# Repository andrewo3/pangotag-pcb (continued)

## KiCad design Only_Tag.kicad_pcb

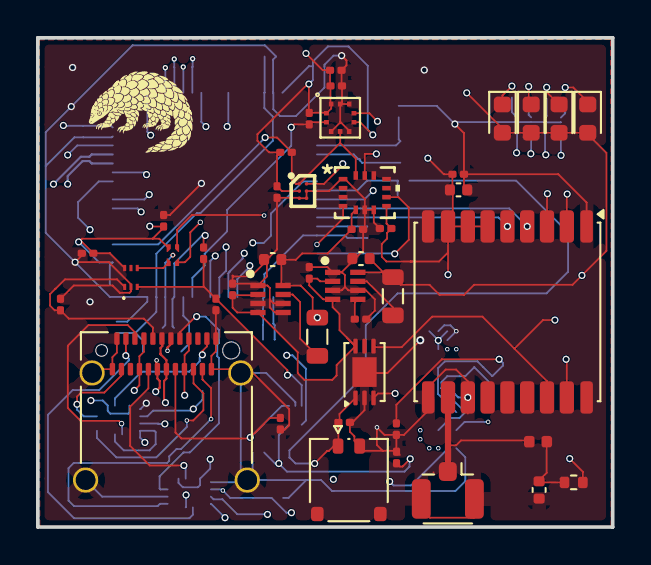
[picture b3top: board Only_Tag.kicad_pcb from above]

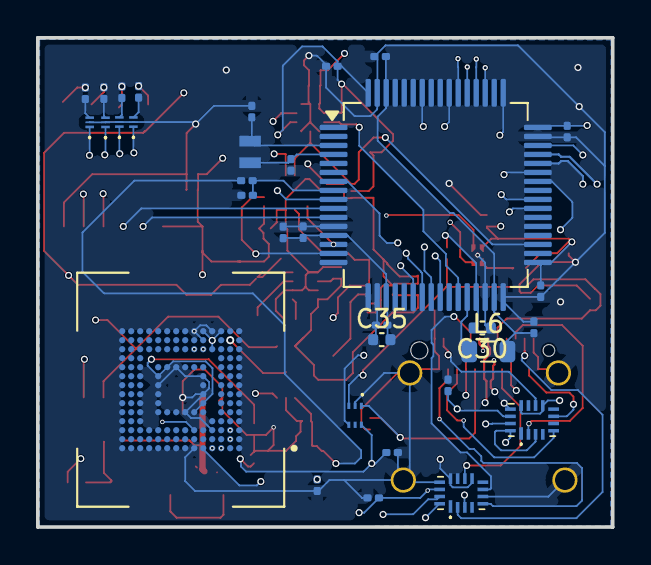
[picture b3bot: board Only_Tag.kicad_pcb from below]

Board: 6 copper layers, 31.9 x 27.2 mm, 77 parts (33 on the bottom side), 64 nets.

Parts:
C1, C2, C3, C10, C15, C18, C20, C21, C23, C26, C27, C28, C29, C31, C32, C36, C37, C39, C40: 100n; C_0201_0603Metric
C4: 10n; C_0402_1005Metric
C7, C8: 4.7u; C_0201_0603Metric
C13: 0.1u; C_0201_0603Metric
C16, C17: 8p; C_0201_0603Metric
C22, C24, C25, C30, C35: 10u; C_0402_1005Metric
C38: 1u; C_0201_0603Metric
C41, C42: 2.2u; C_0201_0603Metric
D1: XZCM2CRK53WA-1VF; LED_0603_1608Metric
D2: XZCM2CYK53WA-1VF; LED_0603_1608Metric
D3: XZCDGK53W-1VF; LED_0603_1608Metric
D4: XZCFBB53W-1VF; LED_0603_1608Metric
IC1, IC2: TLV3691IDPFR
IC3, IC4: TPS62840DLCR; SON50P150X200X100-8N-D
IC5, IC6: TS3A5018RSVR
J1: USB_C_Receptacle; USB_C_Receptacle_Amphenol_12401610E4-2A_CircularHoles
J2: Conn_Coaxial; U.FL_Hirose_U.FL-R-SMT-1_Vertical
J5: Conn_01x02; Hirose_DF57H-2P-1.2V_1x02_P1.2mm_Socket
L1: 27n; L_0402_1005Metric
L5, L6, L7: 2.2u; L_0805_2012Metric
Q1, Q2, Q3, Q4: PMX100UNZ
R1, R2: 10k; R_0201_0603Metric
R3, R4: 5.1k; R_0201_0603Metric
R5: 10; R_0402_1005Metric
R6: 900; R_0201_0603Metric
R7: 725; R_0201_0603Metric
R8, R9: 325; R_0201_0603Metric
R13: 267k; R_0201_0603Metric
R15: 1M; R_0201_0603Metric
R16: 500k; R_0201_0603Metric
R21: 80M; R_0201_0603Metric
R22: 10M; R_0201_0603Metric
U2: NSEC3T016-IT; BGA153N50P14X14_1150X1300X80
U3: SN74AUP1G08DPWR; DPW0005A_TEX
U4: MAX-M10S; ublox_MAX
U7: LTC2941IDCB-1#TRMPBF; DFN-6-1EP_3x2mm_P0.5mm_EP1.65x1.35mm
U8: STM32U585RITxQ; LQFP-64_10x10mm_P0.5mm
U11: AS6221T-AWLT; BGA6C40P2X3_102X150X52
U14: BMP581
U16: BMI270; BMI270_BOS
Y1: CM9V-T1A-32.768KHZ-7PF-20PPM-TA-QC; XTAL_CM9V-T1A-32.768KHZ-7PF-20PPM-TA-QC

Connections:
+3V3: C2.2, C24.1, C29.2, D1.2 (A), D2.2 (A), D3.2 (A), D4.2 (A), IC3.8 (VOS), L5.1, R5.1, U2.E6 (VCC), U2.F5 (VCC), U2.J10 (VCC), U2.K9 (VCC), U8.48 (VDDUSB)
ACC_INT1: U8.14 (PA0), U16.4 (INT1)
ACC_INT2: U8.15 (PA1), U16.9 (INT2)
CC1: IC1.1 (IN+), J1.A5 (CC1), R3.1
CC2: IC2.1 (IN+), J1.B5 (CC2), R4.1
GND: C1.2, C2.1, C3.2, C4.2, C7.2, C8.2, C10.2, C13.2, C15.2, C16.1, C17.1, C18.2, C20.1, C21.2, C22.2, C23.2, C24.2, C25.2, C26.2, C27.2, C28.2, C29.1, C30.1, C31.2, C32.2, C35.1, C36.1, C37.1, C38.1, C39.1, C40.1, C41.2, C42.2, IC1.2 (GND), IC2.2 (GND), IC3.1 (GND), IC3.3 (MODE), IC3.6 (STOP), IC4.1 (GND), IC4.3 (MODE), IC4.5 (VSET), IC4.6 (STOP), IC5.6 (GND), IC5.13 (~EN), IC6.13 (~EN), J1.A1 (GND), J1.A12 (GND), J1.B1 (GND), J1.B12 (GND), J1.SH (SHIELD), J2.2 (Ext), J5.2, Q1.2 (S), Q2.2 (S), Q3.2 (S), Q4.2 (S), R3.2, R4.2, R13.2, R16.2, R22.2, U2.A6 (VSS), U2.C4 (VSSQ), U2.E7 (VSS), U2.G5 (VSS), U2.H10 (VSS), U2.J5 (VSS), U2.K8 (VSS), U2.N2 (VSSQ), U2.N5 (VSSQ), U2.P4 (VSSQ), U2.P6 (VSSQ), U3.3 (GND), U4.1 (GND), U4.10 (GND), U4.12 (GND), U7.2 (GND), U7.7 (EP), U8.12 (VSSA), U8.18 (VSS), U8.30 (VSSSMPS), U8.32 (VSS), U8.47 (VSS), U8.63 (VSS), U11.B2 (VSS), U11.C1 (ADD0), U11.C2 (ALERT), U14.3 (GND), U14.5 (SDO/ADR), U14.8 (GND), U14.9 (GND), U16.1 (SDO), U16.6 (GNDIO), U16.7 (GND)
GPS_EXTINT: U4.5 (EXTINT), U8.11 (PC3)
I2C1_SCL: R1.1, U4.17 (SCL), U7.3 (SCL), U8.27 (PB10), U11.A2 (SCL), U14.2 (SCK/SCL), U16.13 (SCX)
I2C1_SDA: R2.1, U4.16 (SDA), U7.4 (SDA), U8.35 (PB14), U11.A1 (SDA), U14.4 (SDI/SDA), U16.14 (SDX)
LED1: Q1.1 (G), U8.25 (PB1)
LED2: Q2.1 (G), U8.24 (PB0)
LED3: Q3.1 (G), U8.23 (PA7)
LED4: Q4.1 (G), U8.22 (PA6)
NRST: IC5.9 (NC3), IC5.12 (NC4), U8.7 (NRST)
unnamed: C4.1, L1.1, R5.2
unnamed: C41.1, C42.1, L6.2, U8.31 (VDD11), U8.62 (VDD11)
unnamed: D1.1 (K), R6.2
unnamed: D2.1 (K), R7.2
unnamed: D3.1 (K), R8.2
unnamed: D4.1 (K), R9.2
unnamed: IC1.3 (IN-), IC2.3 (IN-), R21.2, R22.1
unnamed: IC1.4 (OUT), U3.1 (A)
unnamed: IC2.4 (OUT), U3.2 (B)
unnamed: IC3.7 (SW), L5.2
unnamed: IC3.5 (VSET), R13.1
unnamed: IC4.7 (SW), L7.2
unnamed: IC5.2 (COM1), J1.A2 (TX1+)
unnamed: IC5.5 (COM2), J1.B2 (TX2+)
unnamed: IC5.7 (COM3), J1.A8 (SBU1)
unnamed: IC5.10 (COM4), J1.B8 (SBU2)
unnamed: IC6.2 (COM1), J1.A3 (TX1-)
unnamed: IC6.5 (COM2), J1.B3 (TX2-)
unnamed: IC6.7 (COM3), J1.B11 (RX1+)
unnamed: IC6.10 (COM4), J1.A11 (RX2+)
unnamed: Q1.3 (D), R6.1
unnamed: Q2.3 (D), R7.1
unnamed: Q3.3 (D), R8.1
unnamed: Q4.3 (D), R9.1
unnamed: C3.1, U2.C2 (VDDi)
OSC32_IN: C17.2, U8.3 (PC14), Y1.2
OSC32_OUT: C16.2, U8.4 (PC15), Y1.1
PRS_INT: U8.9 (PC1), U14.7 (INT)
RF_IN: J2.1 (In), L1.2, U4.11 (RF_IN)
SDMMC1_CK: U2.M6 (CLK), U8.53 (PC12)
SDMMC1_CMD: U2.M5 (CMD), U8.54 (PD2)
SDMMC1_D0: U2.A3 (DAT0), U8.39 (PC8)
SDMMC1_D1: U2.A4 (DAT1), U8.40 (PC9)
SDMMC1_D2: U2.A5 (DAT2), U8.51 (PC10)
SDMMC1_D3: U2.B2 (DAT3), U8.52 (PC11)
SWCLK: IC5.3 (NC2), IC5.16 (NC1), U8.49 (PA14)
SWDIO: IC6.3 (NC2), IC6.16 (NC1), U8.46 (PA13)
SWO: IC6.9 (NC3), IC6.12 (NC4), U8.55 (PB3)
Timepulse: U4.4 (TIMEPULSE), U8.10 (PC2)
USART1_RX: U4.2 (TXD), U8.43 (PA10)
USART1_TX: U4.3 (RXD), U8.58 (PB6)
USBC_FUNCTION: IC5.15 (IN), IC6.15 (IN), U3.4 (Y)
USB_OTG_FS_D+: J1.A6 (D+), J1.B6 (D+), U8.45 (PA12)
USB_OTG_FS_D-: J1.A7 (D-), J1.B7 (D-), U8.44 (PA11)
USB_OTG_VBUS: J1.A4 (VBUS), J1.A9 (VBUS), J1.B4 (VBUS), J1.B9 (VBUS), U8.42 (PA9)
VBAT/3: R15.2, R16.1, U8.8 (PC0)
VDD: C13.1, J5.1, R15.1, U7.1 (SENSE+)
VDD2: C7.1, C8.1, IC3.2 (VIN), IC3.4 (EN), IC4.2 (VIN), IC4.4 (EN), U7.6 (SENSE–)
VDDA: C1.1, C10.1, C15.1, C18.1, C20.2, C21.1, C22.1, C23.1, C25.1, C26.1, C27.1, C28.1, C30.2, C31.1, C32.1, C35.2, C36.2, C37.2, C38.2, C39.2, C40.2, IC1.6 (VCC), IC2.6 (VCC), IC4.8 (VOS), IC5.14 (V+), IC6.14 (V+), L7.1, R1.2, R2.2, R21.1, U2.C6 (VCCQ), U2.M4 (VCCQ), U2.N4 (VCCQ), U2.P3 (VCCQ), U2.P5 (VCCQ), U3.5 (VCC), U4.6 (V_BCKP), U4.7 (VCC_IO), U4.8 (VCC), U8.13 (VDDA), U8.19 (VDD), U8.29 (VDDSMPS), U8.33 (VDD), U8.64 (VDD), U11.B1 (VDD), U14.1 (VDDIO), U14.6 (CSB), U14.10 (VDD), U16.5 (VDDIO), U16.8 (VDD)
VLXSMPS: L6.1, U8.28 (VLXSMPS)

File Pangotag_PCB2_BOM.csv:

"Id";"Designator";"Footprint";"Quantity";"Designation";"Supplier and ref";
1;"BT1, BT2, BT3";"BAT_2996";3;"2996";;;
2;"C1, C2, C3, C10, C15, C18, C20, C21, C23, C26, C27, C28, C29, C31, C32, C36, C37, C39, C40";"C_0201_0603Metric";19;"100n";;;
3;"C7, C8, C11";"C_0201_0603Metric";3;"4.7u";;;
4;"C13";"C_0201_0603Metric";1;"0.1u";;;
5;"C16, C17";"C_0201_0603Metric";2;"8p";;;
6;"C19, C22, C24, C25, C30, C35";"C_0201_0603Metric";6;"10u";;;
7;"C38";"C_0201_0603Metric";1;"1u";;;
8;"C41, C42";"C_0201_0603Metric";2;"2.2u";;;
9;"CN2";"PinHeader_2x03_P2.54mm_Vertical";1;"POGOPIN_2X04_P2.54_M";;;
10;"D1";"LED_0201_0603Metric";1;"XZCM2CRK53WA-1VF";;;
11;"D2";"LED_0201_0603Metric";1;"XZCM2CYK53WA-1VF";;;
12;"D3";"LED_0201_0603Metric";1;"XZCDGK53W-1VF";;;
13;"D4";"LED_0201_0603Metric";1;"XZCFBB53W-1VF";;;
14;"IC1, IC2";"TLV3691IDPFR";2;"TLV3691IDPFR";;;
15;"IC3, IC4";"SON50P150X200X100-8N-D";2;"TPS62840DLCR";;;
16;"IC5, IC6";"TS3A5018RSVR";2;"TS3A5018RSVR";;;
17;"J1";"USB_C_Receptacle_Amphenol_12401610E4-2A_CircularHoles";1;"USB_C_Receptacle";;;
18;"J2";"U.FL_Hirose_U.FL-R-SMT-1_Vertical";1;"Conn_Coaxial";;;
19;"J3";"USB_Mini-B_Lumberg_2486_01_Horizontal";1;"USB_B_Mini";;;
20;"J4";"UP32CFGFL3P24TR";1;"UP32-C-F-G-FL-3-P24-TR";;;
21;"J5, J6, J7";"Hirose_DF57H-2P-1.2V_1x02_P1.2mm_Socket";3;"Conn_01x02";;;
22;"L1";"L_0201_0603Metric";1;"100n";;;
23;"L4, L5, L6, L7";"L_0201_0603Metric";4;"2.2u";;;
24;"Q1, Q2, Q3, Q4";"PMX100UNZ";4;"PMX100UNZ";;;
25;"R1, R2, R12";"R_0201_0603Metric";3;"10k";;;
26;"R3, R4";"R_0201_0603Metric";2;"5.1k";;;
27;"R6";"R_0201_0603Metric";1;"900";;;
28;"R7";"R_0201_0603Metric";1;"725";;;
29;"R8, R9";"R_0201_0603Metric";2;"325";;;
30;"R10, R17";"R_0201_0603Metric";2;"56k";;;
31;"R13";"R_0201_0603Metric";1;"267k";;;
32;"R15";"R_0201_0603Metric";1;"1M";;;
33;"R16";"R_0201_0603Metric";1;"500k";;;
34;"R21";"R_0201_0603Metric";1;"80M";;;
35;"R22";"R_0201_0603Metric";1;"10M";;;
36;"SW1";"SW_SPST_B3U-1000P";1;"SW_Push";;;
37;"U2";"BGA153N50P14X14_1150X1300X80";1;"~";;;
38;"U3";"DPW0005A_TEX";1;"SN74AUP1G08DPWR";;;
39;"U4";"ublox_MAX";1;"MAX-M10S";;;
40;"U7";"DFN-6-1EP_3x2mm_P0.5mm_EP1.65x1.35mm";1;"LTC2941IDCB-1#TRMPBF";;;
41;"U8";"LQFP-64_10x10mm_P0.5mm";1;"STM32U585RITxQ";;;
42;"U11";"BGA6C40P2X3_102X150X52";1;"AS6221T-AWLT";;;
43;"U14";"BMP581";1;"BMP581";;;
44;"U16";"BMI270_BOS";1;"BMI270";;;
45;"U18";"BGA6N40P3X2_146X96X50N";1;"TPS62840YBGR";;;
46;"Y1";"XTAL_CM9V-T1A-32.768KHZ-7PF-20PPM-TA-QC";1;"CM9V-T1A-32.768KHZ-7PF-20PPM-TA-QC";;;

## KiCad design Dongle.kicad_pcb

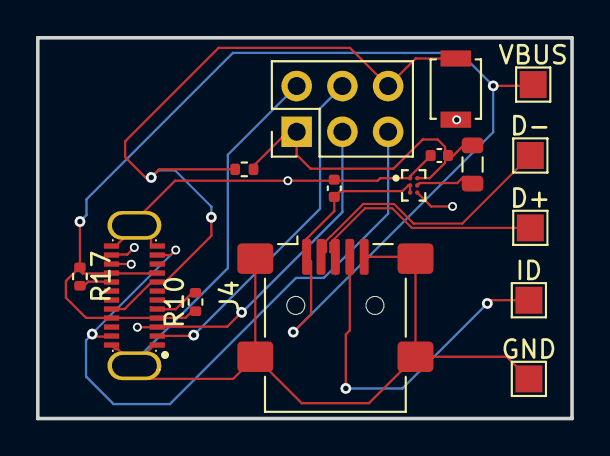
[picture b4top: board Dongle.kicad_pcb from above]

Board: 4 copper layers, 29.7 x 21.2 mm, 16 parts (0 on the bottom side), 13 nets.

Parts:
C11: 4.7u; C_0402_1005Metric
C19: 10u; C_0402_1005Metric
CN2: POGOPIN_2X04_P2.54_M; PinHeader_2x03_P2.54mm_Vertical
D+: MountingHole_Pad; TestPoint_Pad_1.5x1.5mm
D-: MountingHole_Pad; TestPoint_Pad_1.5x1.5mm
GND: MountingHole_Pad; TestPoint_Pad_1.5x1.5mm
ID: MountingHole_Pad; TestPoint_Pad_1.5x1.5mm
J3: USB_B_Mini; USB_Mini-B_Lumberg_2486_01_Horizontal
J4: UP32-C-F-G-FL-3-P24-TR; USB-TH-TYPE-C_00702-UCAM002-X
L4: 2.2u; L_0805_2012Metric
R10, R17: 56k; R_0402_1005Metric
R12: 10k; R_0402_1005Metric
SW1: SW_Push; SW_SPST_B3U-1000P
U18: TPS62840YBGR; BGA6N40P3X2_146X96X50N
VBUS: MountingHole_Pad; TestPoint_Pad_1.5x1.5mm

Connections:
+1V8_2: C19.1, CN2.1, L4.2, R12.1, U18.A2 (VOS)
GND2: C11.2, C19.2, CN2.2, GND.1 (1_1), J3.5 (GND), J3.SH (Shield), J4.14, J4.A1 (GND_1), J4.A12 (GND_2), J4.B1 (GND_3), J4.B12 (GND_4), SW1.2, U18.A1 (GND), U18.C2 (VSET)
NRST_OUT: CN2.6, J4.A8 (SBU1), J4.B8 (SBU2), R12.2, SW1.1
unnamed: ID.1 (1_1), J3.4 (ID)
unnamed: J4.A5 (CC1), R10.2
unnamed: J4.B5 (CC2), R17.2
unnamed: L4.1, U18.B2 (SW)
ST_D+: D+.1 (1_1), J3.3 (D+)
ST_D-: D-.1 (1_1), J3.2 (D-)
SWCLK_OUT: CN2.4, J4.A2 (SSTXP1), J4.B2 (SSTXP2)
SWDIO_OUT: CN2.3, J4.A3 (SSTXN1), J4.B3 (SSTXN2)
SWO_OUT: CN2.5, J4.A11 (SSRXP2), J4.B11 (SSRXP1)
VBUS_DONGLE: C11.1, J3.1 (VBUS), J4.A4 (VBUS_1), J4.A9 (VBUS_2), J4.B4 (VBUS_3), J4.B9 (VBUS_4), R10.1, R17.1, U18.B1 (VIN), U18.C1 (EN), VBUS.1 (1_1)

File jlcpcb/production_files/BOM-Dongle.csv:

Comment,Designator,Footprint,LCSC,Quantity
10k,R12,R_0402_1005Metric,C60489,1
10u,C19,C_0402_1005Metric,C15525,1
2.2u,L4,L_0805_2012Metric,C98033,1
4.7u,C11,C_0402_1005Metric,C23733,1
56k,"R10,R17",R_0402_1005Metric,C25567,2
POGOPIN_2X04_P2.54_M,CN2,PinHeader_2x03_P2.54mm_Vertical,C239343,1
SW_Push,SW1,SW_SPST_B3U-1000P,C231329,1
TPS62840YBGR,U18,BGA6N40P3X2_146X96X50N,C2071139,1
UP32-C-F-G-FL-3-P24-TR,J4,USB-TH-TYPE-C_00702-UCAM002-X,C3148227,1
USB_B_Mini,J3,USB_Mini-B_Lumberg_2486_01_Horizontal,C46391,1
